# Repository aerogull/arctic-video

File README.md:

# Arctic-Video
#### An FPGA card designed around video, audio, and PCIe.
Built on a Xilinx Artix-7 75T FPGA chip, with jtag programming, video and audio ports on the card, and DDR3L RAM.

- XC7A75T-2FGG676C
- 256Mb spi flash
- 1GB DDR3L RAM
- 2 6G-SDI ports
- 1 2-lane DisplayPort
- PCIe gen 2 x4 interface
- JTAG programming
- 6 status LEDs

This hardware is untested, use the designs at your own risk!

An interactive bom, which includes jlc estimated prices, can be found in the ibom.html file in root. There is a full blend file and a file for the pcb bracket in the cad folder.

JLCPCB estimates:

PCB production costs $165.41

PCBA costs $392.47

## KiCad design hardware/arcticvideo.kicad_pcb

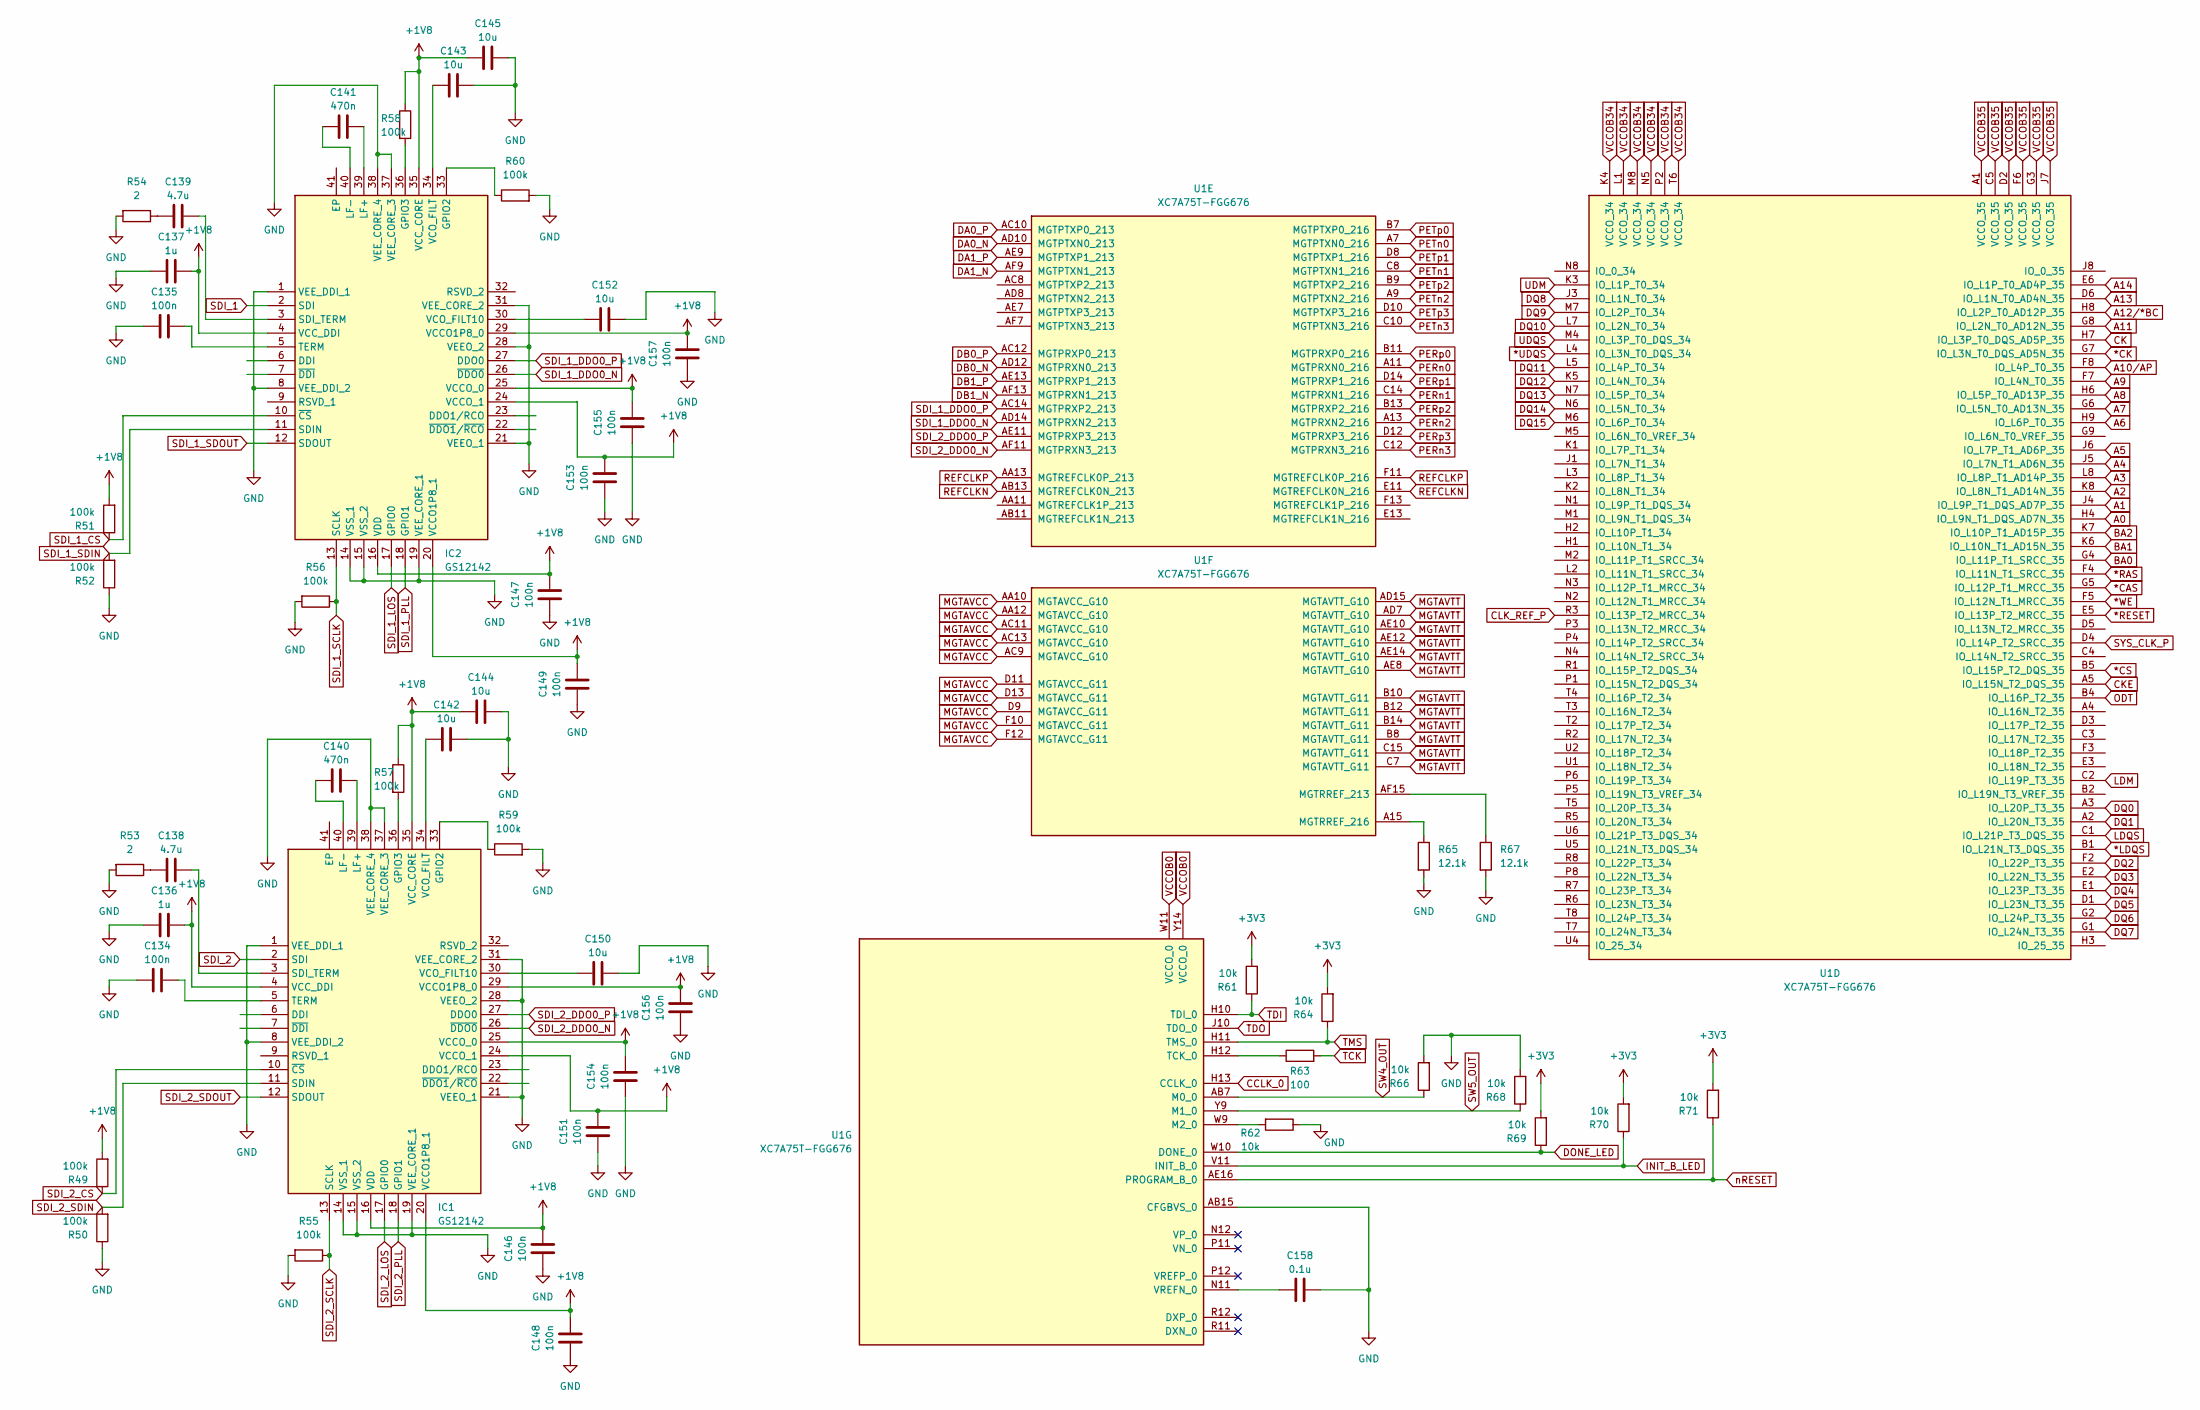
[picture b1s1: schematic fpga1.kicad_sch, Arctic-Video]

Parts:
C134, C135, C146, C147, C148, C149, C151, C153, C154, C155, C156, C157: 100n; C_0402_1005Metric
C136, C137: 1u; C_0402_1005Metric
C138, C139: 4.7u; C_0402_1005Metric
C140, C141: 470n; C_0402_1005Metric
C142, C143, C144, C145, C150, C152: 10u; C_0402_1005Metric
C158: 0.1u; C_0402_1005Metric
IC1, IC2: GS12142; QFN40P400X600X100-41N-D; Manufacturer_Part_Number GS12142
R49, R50, R51, R52, R55, R56, R57, R58, R59, R60: 100k; R_0402_1005Metric
R53, R54: 2; R_0402_1005Metric
R61, R62, R64, R66, R68, R69, R70, R71: 10k; R_0402_1005Metric
R63: 100; R_0402_1005Metric
R65, R67: 12.1k; R_0402_1005Metric
U1: XC7A75T-FGG676; Xilinx_FGG676

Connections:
*CAS: U1.G5 (IO_L12P_T1_MRCC_35); also elsewhere on the board
*CK: U1.G7 (IO_L3N_T0_DQS_AD5N_35); also elsewhere on the board
*CS: U1.B5 (IO_L15P_T2_DQS_35); also elsewhere on the board
*LDQS: U1.B1 (IO_L21N_T3_DQS_35); also elsewhere on the board
*RAS: U1.F4 (IO_L11N_T1_SRCC_35); also elsewhere on the board
*RESET: U1.E5 (IO_L13P_T2_MRCC_35); also elsewhere on the board
*UDQS: U1.L4 (IO_L3N_T0_DQS_34); also elsewhere on the board
*WE: U1.F5 (IO_L12N_T1_MRCC_35); also elsewhere on the board
A0: U1.H4 (IO_L9N_T1_DQS_AD7N_35); also elsewhere on the board
A1: U1.J4 (IO_L9P_T1_DQS_AD7P_35); also elsewhere on the board
A2: U1.K8 (IO_L8N_T1_AD14N_35); also elsewhere on the board
A3: U1.L8 (IO_L8P_T1_AD14P_35); also elsewhere on the board
A4: U1.J5 (IO_L7N_T1_AD6N_35); also elsewhere on the board
A5: U1.J6 (IO_L7P_T1_AD6P_35); also elsewhere on the board
A6: U1.H9 (IO_L6P_T0_35); also elsewhere on the board
A7: U1.G6 (IO_L5N_T0_AD13N_35); also elsewhere on the board
A8: U1.H6 (IO_L5P_T0_AD13P_35); also elsewhere on the board
A9: U1.F7 (IO_L4N_T0_35); also elsewhere on the board
A10/AP: U1.F8 (IO_L4P_T0_35); also elsewhere on the board
A11: U1.G8 (IO_L2N_T0_AD12N_35); also elsewhere on the board
A12/*BC: U1.H8 (IO_L2P_T0_AD12P_35); also elsewhere on the board
A13: U1.D6 (IO_L1N_T0_AD4N_35); also elsewhere on the board
A14: U1.E6 (IO_L1P_T0_AD4P_35); also elsewhere on the board
BA0: U1.G4 (IO_L11P_T1_SRCC_35); also elsewhere on the board
BA1: U1.K6 (IO_L10N_T1_AD15N_35); also elsewhere on the board
BA2: U1.K7 (IO_L10P_T1_AD15P_35); also elsewhere on the board
CCLK_0: U1.H13 (CCLK_0); also elsewhere on the board
CK: U1.H7 (IO_L3P_T0_DQS_AD5P_35); also elsewhere on the board
CKE: U1.A5 (IO_L15N_T2_DQS_35); also elsewhere on the board
CLK_REF_P: U1.D4 (IO_L14P_T2_SRCC_35), U1.R3 (IO_L13P_T2_MRCC_34); also elsewhere on the board
DA0_N: U1.AD10 (MGTPTXN0_213); also elsewhere on the board
DA0_P: U1.AC10 (MGTPTXP0_213); also elsewhere on the board
DA1_N: U1.AF9 (MGTPTXN1_213); also elsewhere on the board
DA1_P: U1.AE9 (MGTPTXP1_213); also elsewhere on the board
DB0_N: U1.AD12 (MGTPRXN0_213); also elsewhere on the board
DB0_P: U1.AC12 (MGTPRXP0_213); also elsewhere on the board
DB1_N: U1.AF13 (MGTPRXN1_213); also elsewhere on the board
DB1_P: U1.AE13 (MGTPRXP1_213); also elsewhere on the board
DONE_LED: R69.1, U1.W10 (DONE_0); also elsewhere on the board
DQ0: U1.A3 (IO_L20P_T3_35); also elsewhere on the board
DQ1: U1.A2 (IO_L20N_T3_35); also elsewhere on the board
DQ2: U1.F2 (IO_L22P_T3_35); also elsewhere on the board
DQ3: U1.E2 (IO_L22N_T3_35); also elsewhere on the board
DQ4: U1.E1 (IO_L23P_T3_35); also elsewhere on the board
DQ5: U1.D1 (IO_L23N_T3_35); also elsewhere on the board
DQ6: U1.G2 (IO_L24P_T3_35); also elsewhere on the board
DQ7: U1.G1 (IO_L24N_T3_35); also elsewhere on the board
DQ8: U1.J3 (IO_L1N_T0_34); also elsewhere on the board
DQ9: U1.M7 (IO_L2P_T0_34); also elsewhere on the board
DQ10: U1.L7 (IO_L2N_T0_34); also elsewhere on the board
DQ11: U1.L5 (IO_L4P_T0_34); also elsewhere on the board
DQ12: U1.K5 (IO_L4N_T0_34); also elsewhere on the board
DQ13: U1.N7 (IO_L5P_T0_34); also elsewhere on the board
DQ14: U1.N6 (IO_L5N_T0_34); also elsewhere on the board
DQ15: U1.M6 (IO_L6P_T0_34); also elsewhere on the board
GND: C134.1, C135.1, C136.1, C137.1, C142.2, C143.2, C144.2, C145.2, C146.1, C147.1, C148.1, C149.1, C150.2, C151.1, C152.2, C153.1, C154.1, C155.1, C156.1, C157.1, C158.2, IC1.1 (VEE_DDI_1), IC1.8 (VEE_DDI_2), IC1.14 (VSS_1), IC1.15 (VSS_2), IC1.19 (VEE_CORE_1), IC1.21 (VEEO_1), IC1.28 (VEEO_2), IC1.31 (VEE_CORE_2), IC1.37 (VEE_CORE_3), IC1.38 (VEE_CORE_4), IC2.1 (VEE_DDI_1), IC2.8 (VEE_DDI_2), IC2.14 (VSS_1), IC2.15 (VSS_2), IC2.19 (VEE_CORE_1), IC2.21 (VEEO_1), IC2.28 (VEEO_2), IC2.31 (VEE_CORE_2), IC2.37 (VEE_CORE_3), IC2.38 (VEE_CORE_4), R50.1, R52.1, R53.2, R54.2, R55.2, R56.2, R59.2, R60.2, R62.1, R65.2, R66.2, R67.2, R68.2, U1.AB15 (CFGBVS_0); also elsewhere on the board
INIT_B_LED: R70.1, U1.V11 (INIT_B_0); also elsewhere on the board
LDM: U1.C2 (IO_L19P_T3_35); also elsewhere on the board
LDQS: U1.C1 (IO_L21P_T3_DQS_35); also elsewhere on the board
MGTAVCC: U1.AA10 (MGTAVCC_G10), U1.AA12 (MGTAVCC_G10), U1.AC9 (MGTAVCC_G10), U1.AC11 (MGTAVCC_G10), U1.AC13 (MGTAVCC_G10), U1.D9 (MGTAVCC_G11), U1.D11 (MGTAVCC_G11), U1.D13 (MGTAVCC_G11), U1.F10 (MGTAVCC_G11), U1.F12 (MGTAVCC_G11); also elsewhere on the board
MGTAVTT: U1.AD7 (MGTAVTT_G10), U1.AD15 (MGTAVTT_G10), U1.AE8 (MGTAVTT_G10), U1.AE10 (MGTAVTT_G10), U1.AE12 (MGTAVTT_G10), U1.AE14 (MGTAVTT_G10), U1.B8 (MGTAVTT_G11), U1.B10 (MGTAVTT_G11), U1.B12 (MGTAVTT_G11), U1.B14 (MGTAVTT_G11), U1.C7 (MGTAVTT_G11), U1.C15 (MGTAVTT_G11); also elsewhere on the board
unnamed: C138.1, R53.1
unnamed: C139.1, R54.1
unnamed: IC1.33 (GPIO2), R59.1
unnamed: IC1.36 (GPIO3), R57.2
unnamed: C140.2, IC1.39 (LF+)
unnamed: C140.1, IC1.40 (LF-)
unnamed: C138.2, IC1.3 (SDI_TERM)
unnamed: C134.2, IC1.5 (TERM)
unnamed: C150.1, IC1.30 (VCO_FILT10)
unnamed: C142.1, IC1.34 (VCO_FILT)
unnamed: IC2.33 (GPIO2), R60.1
unnamed: IC2.36 (GPIO3), R58.2
unnamed: C141.2, IC2.39 (LF+)
unnamed: C141.1, IC2.40 (LF-)
unnamed: C139.2, IC2.3 (SDI_TERM)
unnamed: C135.2, IC2.5 (TERM)
unnamed: C152.1, IC2.30 (VCO_FILT10)
unnamed: C143.1, IC2.34 (VCO_FILT)
unnamed: R67.1, U1.AF15 (MGTRREF_213)
unnamed: R65.1, U1.A15 (MGTRREF_216)
unnamed: R62.2, U1.W9 (M2_0)
unnamed: R63.1, U1.H12 (TCK_0)
unnamed: C158.1, U1.N11 (VREFN_0)
ODT: U1.B4 (IO_L16P_T2_35); also elsewhere on the board
PERn0: U1.A11 (MGTPRXN0_216); also elsewhere on the board
PERn1: U1.C14 (MGTPRXN1_216); also elsewhere on the board
PERn2: U1.A13 (MGTPRXN2_216); also elsewhere on the board
PERn3: U1.C12 (MGTPRXN3_216); also elsewhere on the board
PERp0: U1.B11 (MGTPRXP0_216); also elsewhere on the board
PERp1: U1.D14 (MGTPRXP1_216); also elsewhere on the board
PERp2: U1.B13 (MGTPRXP2_216); also elsewhere on the board
PERp3: U1.D12 (MGTPRXP3_216); also elsewhere on the board
PETn0: U1.A7 (MGTPTXN0_216); also elsewhere on the board
PETn1: U1.C8 (MGTPTXN1_216); also elsewhere on the board
PETn2: U1.A9 (MGTPTXN2_216); also elsewhere on the board
PETn3: U1.C10 (MGTPTXN3_216); also elsewhere on the board
PETp0: U1.B7 (MGTPTXP0_216); also elsewhere on the board
PETp1: U1.D8 (MGTPTXP1_216); also elsewhere on the board
PETp2: U1.B9 (MGTPTXP2_216); also elsewhere on the board
PETp3: U1.D10 (MGTPTXP3_216); also elsewhere on the board
REFCLKN: U1.AB13 (MGTREFCLK0N_213), U1.E11 (MGTREFCLK0N_216); also elsewhere on the board
REFCLKP: U1.AA13 (MGTREFCLK0P_213), U1.F11 (MGTREFCLK0P_216); also elsewhere on the board
SDI_1: IC2.2 (SDI); also elsewhere on the board
SDI_1_CS: IC2.10 (~CS), R51.1; also elsewhere on the board
SDI_1_DDO0_N: IC2.26 (~DDO0), U1.AD14 (MGTPRXN2_213)
SDI_1_DDO0_P: IC2.27 (DDO0), U1.AC14 (MGTPRXP2_213)
SDI_1_LOS: IC2.17 (GPIO0); also elsewhere on the board
SDI_1_PLL: IC2.18 (GPIO1); also elsewhere on the board
SDI_1_SCLK: IC2.13 (SCLK), R56.1; also elsewhere on the board
SDI_1_SDIN: IC2.11 (SDIN), R52.2; also elsewhere on the board
SDI_1_SDOUT: IC2.12 (SDOUT); also elsewhere on the board
SDI_2: IC1.2 (SDI); also elsewhere on the board
SDI_2_CS: IC1.10 (~CS), R49.1; also elsewhere on the board
SDI_2_DDO0_N: IC1.26 (~DDO0), U1.AF11 (MGTPRXN3_213)
SDI_2_DDO0_P: IC1.27 (DDO0), U1.AE11 (MGTPRXP3_213)
SDI_2_LOS: IC1.17 (GPIO0); also elsewhere on the board
SDI_2_PLL: IC1.18 (GPIO1); also elsewhere on the board
SDI_2_SCLK: IC1.13 (SCLK), R55.1; also elsewhere on the board
SDI_2_SDIN: IC1.11 (SDIN), R50.2; also elsewhere on the board
SDI_2_SDOUT: IC1.12 (SDOUT); also elsewhere on the board
SW4_OUT: R66.1, U1.AB7 (M0_0); also elsewhere on the board
SW5_OUT: R68.1, U1.Y9 (M1_0); also elsewhere on the board
TCK: R63.2; also elsewhere on the board
TDI: R61.1, U1.H10 (TDI_0); also elsewhere on the board
TDO: U1.J10 (TDO_0); also elsewhere on the board
TMS: R64.1, U1.H11 (TMS_0); also elsewhere on the board
UDM: U1.K3 (IO_L1P_T0_34); also elsewhere on the board
UDQS: U1.M4 (IO_L3P_T0_DQS_34); also elsewhere on the board
VCCAUX: C136.2, C137.2, C144.1, C145.1, C146.2, C147.2, C148.2, C149.2, C151.2, C153.2, C154.2, C155.2, C156.2, C157.2, IC1.4 (VCC_DDI), IC1.16 (VDD), IC1.20 (VCCO1P8_1), IC1.24 (VCCO_1), IC1.25 (VCCO_0), IC1.29 (VCCO1P8_0), IC1.35 (VCC_CORE), IC2.4 (VCC_DDI), IC2.16 (VDD), IC2.20 (VCCO1P8_1), IC2.24 (VCCO_1), IC2.25 (VCCO_0), IC2.29 (VCCO1P8_0), IC2.35 (VCC_CORE), R49.2, R51.2, R57.1, R58.1; also elsewhere on the board
VCCOB0: R61.2, R64.2, R69.2, R70.2, R71.2, U1.W11 (VCCO_0), U1.Y14 (VCCO_0); also elsewhere on the board
VCCOB33: U1.A1 (VCCO_35), U1.C5 (VCCO_35), U1.D2 (VCCO_35), U1.F6 (VCCO_35), U1.G3 (VCCO_35), U1.J7 (VCCO_35), U1.K4 (VCCO_34), U1.L1 (VCCO_34), U1.M8 (VCCO_34), U1.N5 (VCCO_34), U1.P2 (VCCO_34), U1.T6 (VCCO_34); also elsewhere on the board
nRESET: R71.1, U1.AE16 (PROGRAM_B_0); also elsewhere on the board

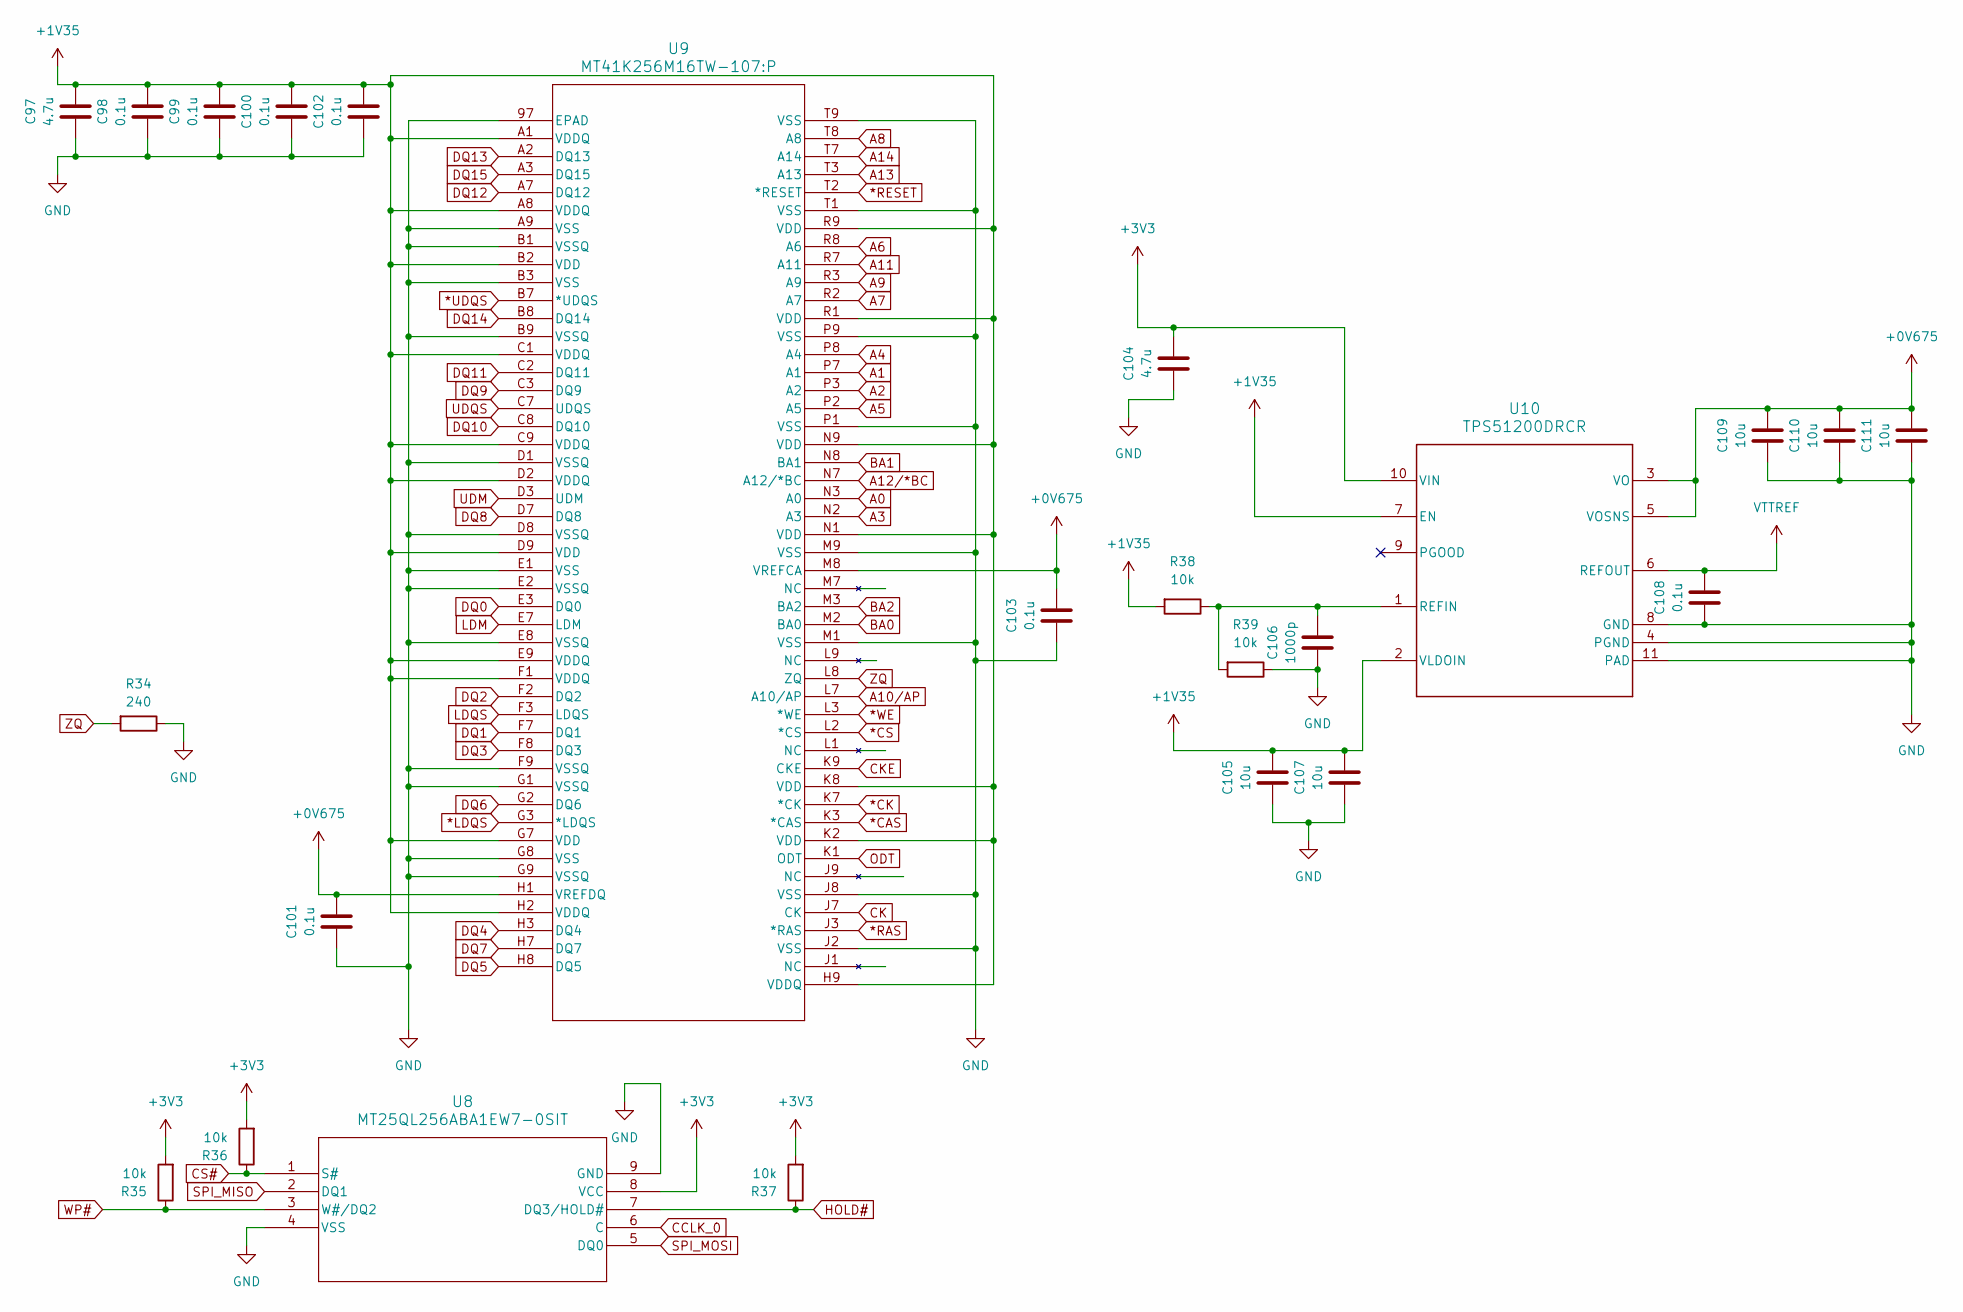
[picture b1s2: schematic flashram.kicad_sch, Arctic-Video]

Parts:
C97, C104: 4.7u; C_0402_1005Metric
C98, C99, C100, C101, C102, C103, C108: 0.1u; C_0402_1005Metric
C105, C107, C109, C110, C111: 10u; C_0402_1005Metric
C106: 1000p; C_0402_1005Metric
R34: 240; R_0402_1005Metric
R35, R36, R37, R38, R39: 10k; R_0402_1005Metric
U8: MT25QL256ABA1EW7-0SIT; SON_EW7-0SIT_MRN
U9: MT41K256M16TW-107:P; FBGA96_8X14_MRN
U10: TPS51200DRCR; DRC0010J

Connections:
*CAS: U9.K3 (*CAS); also elsewhere on the board
*CK: U9.K7 (*CK); also elsewhere on the board
*CS: U9.L2 (*CS); also elsewhere on the board
*LDQS: U9.G3 (*LDQS); also elsewhere on the board
*RAS: U9.J3 (*RAS); also elsewhere on the board
*RESET: U9.T2 (*RESET); also elsewhere on the board
*UDQS: U9.B7 (*UDQS); also elsewhere on the board
*WE: U9.L3 (*WE); also elsewhere on the board
+0V675: C101.2, C103.2, C109.2, C110.2, C111.2, U9.H1 (VREFDQ), U9.M8 (VREFCA), U10.3 (VO), U10.5 (VOSNS)
A0: U9.N3 (A0); also elsewhere on the board
A1: U9.P7 (A1); also elsewhere on the board
A2: U9.P3 (A2); also elsewhere on the board
A3: U9.N2 (A3); also elsewhere on the board
A4: U9.P8 (A4); also elsewhere on the board
A5: U9.P2 (A5); also elsewhere on the board
A6: U9.R8 (A6); also elsewhere on the board
A7: U9.R2 (A7); also elsewhere on the board
A8: U9.T8 (A8); also elsewhere on the board
A9: U9.R3 (A9); also elsewhere on the board
A10/AP: U9.L7 (A10/AP); also elsewhere on the board
A11: U9.R7 (A11); also elsewhere on the board
A12/*BC: U9.N7 (A12/*BC); also elsewhere on the board
A13: U9.T3 (A13); also elsewhere on the board
A14: U9.T7 (A14); also elsewhere on the board
BA0: U9.M2 (BA0); also elsewhere on the board
BA1: U9.N8 (BA1); also elsewhere on the board
BA2: U9.M3 (BA2); also elsewhere on the board
CCLK_0: U8.6 (C); also elsewhere on the board
CK: U9.J7 (CK); also elsewhere on the board
CKE: U9.K9 (CKE); also elsewhere on the board
CS#: R36.1, U8.1 (S#); also elsewhere on the board
DQ0: U9.E3 (DQ0); also elsewhere on the board
DQ1: U9.F7 (DQ1); also elsewhere on the board
DQ2: U9.F2 (DQ2); also elsewhere on the board
DQ3: U9.F8 (DQ3); also elsewhere on the board
DQ4: U9.H3 (DQ4); also elsewhere on the board
DQ5: U9.H8 (DQ5); also elsewhere on the board
DQ6: U9.G2 (DQ6); also elsewhere on the board
DQ7: U9.H7 (DQ7); also elsewhere on the board
DQ8: U9.D7 (DQ8); also elsewhere on the board
DQ9: U9.C3 (DQ9); also elsewhere on the board
DQ10: U9.C8 (DQ10); also elsewhere on the board
DQ11: U9.C2 (DQ11); also elsewhere on the board
DQ12: U9.A7 (DQ12); also elsewhere on the board
DQ13: U9.A2 (DQ13); also elsewhere on the board
DQ14: U9.B8 (DQ14); also elsewhere on the board
DQ15: U9.A3 (DQ15); also elsewhere on the board
GND: C97.1, C98.1, C99.1, C100.1, C101.1, C102.1, C103.1, C104.1, C105.1, C106.1, C107.1, C108.1, C109.1, C110.1, C111.1, R34.1, R39.1, U8.4 (VSS), U8.9 (GND), U9.97 (EPAD), U9.A9 (VSS), U9.B1 (VSSQ), U9.B3 (VSS), U9.B9 (VSSQ), U9.D1 (VSSQ), U9.D8 (VSSQ), U9.E1 (VSS), U9.E2 (VSSQ), U9.E8 (VSSQ), U9.F9 (VSSQ), U9.G1 (VSSQ), U9.G8 (VSS), U9.G9 (VSSQ), U9.J2 (VSS), U9.J8 (VSS), U9.M1 (VSS), U9.M9 (VSS), U9.P1 (VSS), U9.P9 (VSS), U9.T1 (VSS), U9.T9 (VSS), U10.4 (PGND), U10.8 (GND), U10.11 (PAD); also elsewhere on the board
HOLD#: R37.1, U8.7 (DQ3/HOLD#); also elsewhere on the board
LDM: U9.E7 (LDM); also elsewhere on the board
LDQS: U9.F3 (LDQS); also elsewhere on the board
unnamed: C106.2, R38.1, R39.2, U10.1 (REFIN)
ODT: U9.K1 (ODT); also elsewhere on the board
SPI_MISO: U8.2 (DQ1); also elsewhere on the board
SPI_MOSI: U8.5 (DQ0); also elsewhere on the board
UDM: U9.D3 (UDM); also elsewhere on the board
UDQS: U9.C7 (UDQS); also elsewhere on the board
VCCOB0: C104.2, R35.2, R36.2, R37.2, U8.8 (VCC), U10.10 (VIN); also elsewhere on the board
VCCOB33: C97.2, C98.2, C99.2, C100.2, C102.2, C105.2, C107.2, R38.2, U9.A1 (VDDQ), U9.A8 (VDDQ), U9.B2 (VDD), U9.C1 (VDDQ), U9.C9 (VDDQ), U9.D2 (VDDQ), U9.D9 (VDD), U9.E9 (VDDQ), U9.F1 (VDDQ), U9.G7 (VDD), U9.H2 (VDDQ), U9.H9 (VDDQ), U9.K2 (VDD), U9.K8 (VDD), U9.N1 (VDD), U9.N9 (VDD), U9.R1 (VDD), U9.R9 (VDD), U10.2 (VLDOIN), U10.7 (EN); also elsewhere on the board
VTTREF: C108.2, U10.6 (REFOUT)
WP#: R35.1, U8.3 (W#/DQ2); also elsewhere on the board
ZQ: R34.2, U9.L8 (ZQ)

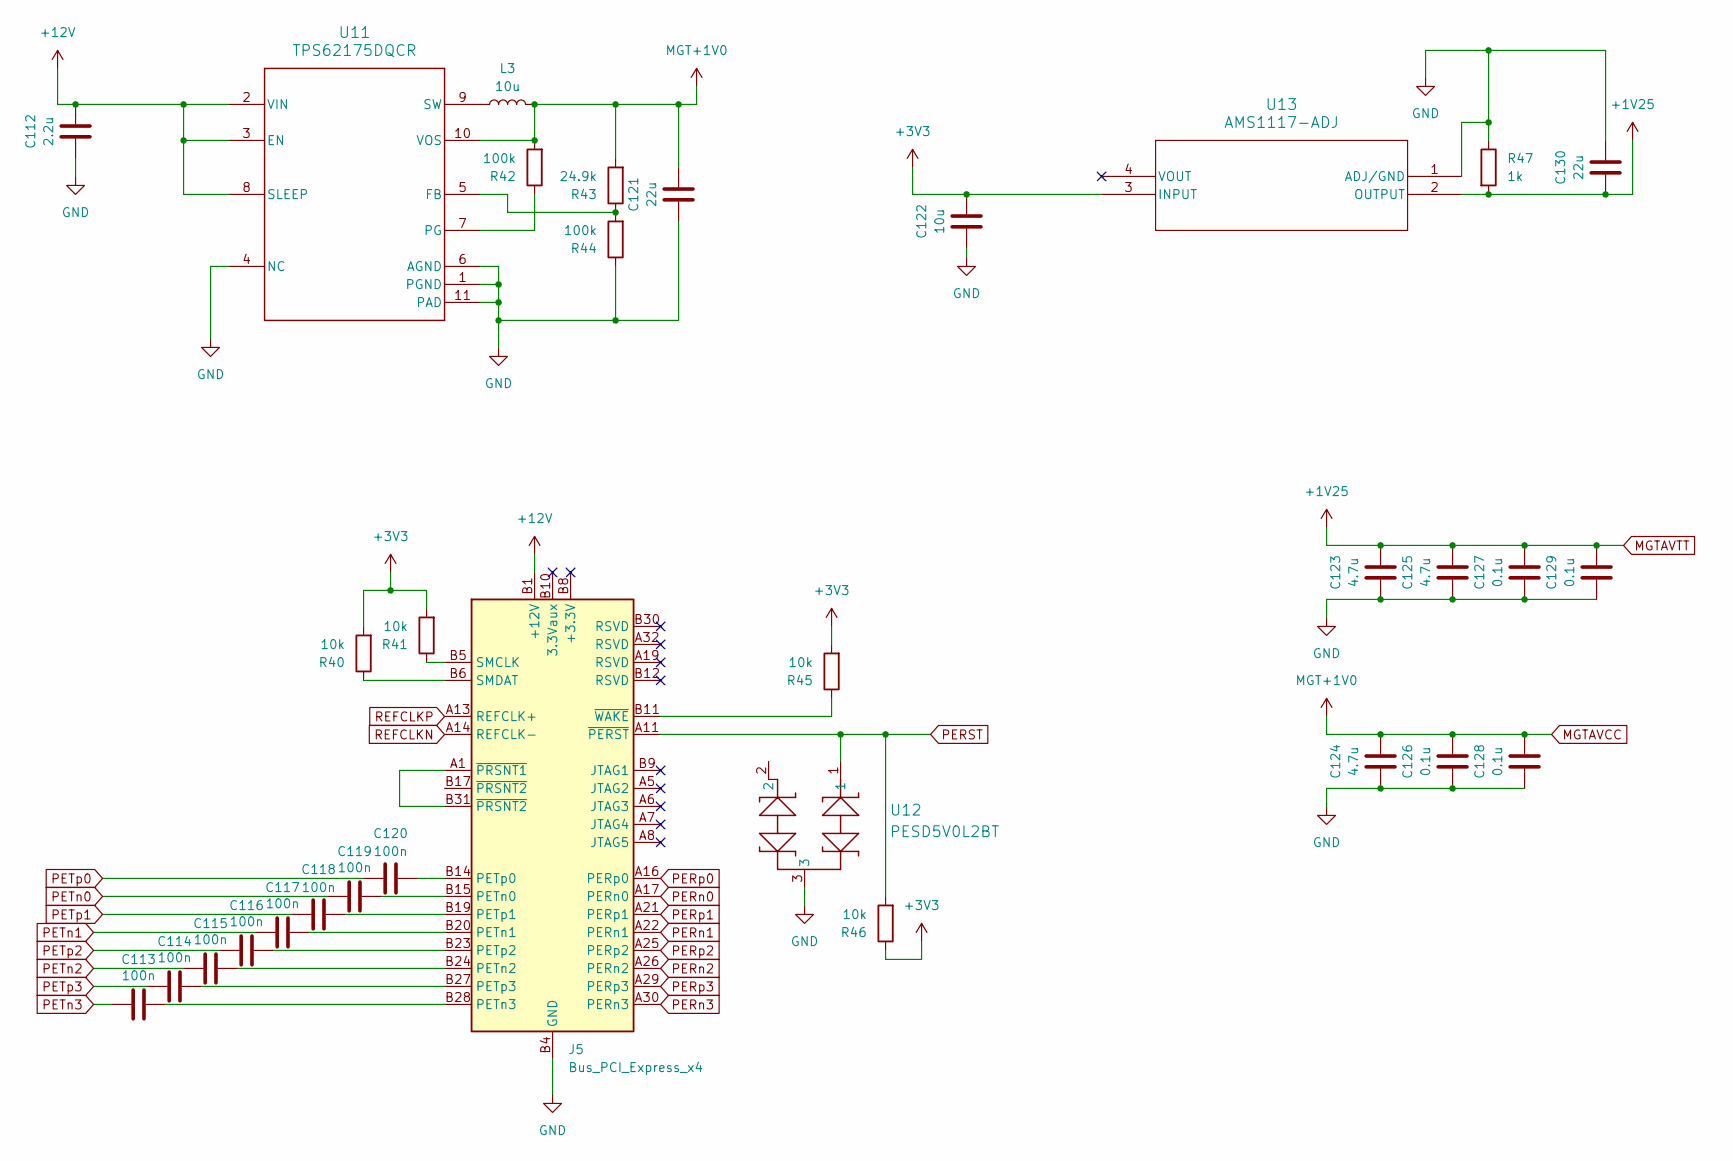
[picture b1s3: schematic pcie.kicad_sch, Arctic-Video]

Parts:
C112: 2.2u; C_0402_1005Metric
C113, C114, C115, C116, C117, C118, C119, C120: 100n; C_0402_1005Metric
C121, C130: 22u; C_0402_1005Metric
C122: 10u; C_0402_1005Metric
C123, C124, C125: 4.7u; C_0402_1005Metric
C126, C127, C128, C129: 0.1u; C_0402_1005Metric
J5: Bus_PCI_Express_x4; BUS_PCIexpress_x4
L3: 10u; L_0402_1005Metric
R40, R41, R45, R46: 10k; R_0402_1005Metric
R42, R44: 100k; R_0402_1005Metric
R43: 24.9k; R_0402_1005Metric
R47: 1k; R_0402_1005Metric
U11: TPS62175DQCR; DQC0010A
U12: PESD5V0L2BT; SOT23_NEX
U13: AMS1117-ADJ; SOT_AMS1117-2.5_AMS

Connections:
+12V: C112.2, J5.A2 (+12V), J5.A3 (+12V), J5.B1 (+12V), J5.B2 (+12V), J5.B3 (+12V), U11.2 (VIN), U11.3 (EN), U11.8 (SLEEP); also elsewhere on the board
GND: C112.1, C121.1, C122.1, C123.1, C124.1, C125.1, C126.1, C127.1, C128.1, C129.1, C130.2, J5.A4 (GND), J5.A12 (GND), J5.A15 (GND), J5.A18 (GND), J5.A20 (GND), J5.A23 (GND), J5.A24 (GND), J5.A27 (GND), J5.A28 (GND), J5.A31 (GND), J5.B4 (GND), J5.B7 (GND), J5.B13 (GND), J5.B16 (GND), J5.B18 (GND), J5.B21 (GND), J5.B22 (GND), J5.B25 (GND), J5.B26 (GND), J5.B29 (GND), J5.B32 (GND), R44.1, R47.1, U11.1 (PGND), U11.4 (NC), U11.6 (AGND), U11.11 (PAD), U12.3, U13.1 (ADJ/GND); also elsewhere on the board
MGTAVCC: C121.2, C124.2, C126.2, C128.2, L3.2, R42.2, R43.2, U11.10 (VOS); also elsewhere on the board
MGTAVTT: C123.2, C125.2, C127.2, C129.2, C130.1, R47.2, U13.2 (OUTPUT); also elsewhere on the board
unnamed: C119.2, J5.B15 (PETn0)
unnamed: C117.2, J5.B20 (PETn1)
unnamed: C115.2, J5.B24 (PETn2)
unnamed: C113.2, J5.B28 (PETn3)
unnamed: C120.2, J5.B14 (PETp0)
unnamed: C118.2, J5.B19 (PETp1)
unnamed: C116.2, J5.B23 (PETp2)
unnamed: C114.2, J5.B27 (PETp3)
unnamed: J5.B5 (SMCLK), R41.1
unnamed: J5.B6 (SMDAT), R40.1
unnamed: J5.A1 (~PRSNT1), J5.B31 (~PRSNT2)
unnamed: J5.B11 (~WAKE), R45.1
unnamed: R43.1, R44.2, U11.5 (FB)
unnamed: R42.1, U11.7 (PG)
unnamed: L3.1, U11.9 (SW)
PERST: J5.A11 (~PERST), R46.2, U12.1; also elsewhere on the board
PERn0: J5.A17 (PERn0); also elsewhere on the board
PERn1: J5.A22 (PERn1); also elsewhere on the board
PERn2: J5.A26 (PERn2); also elsewhere on the board
PERn3: J5.A30 (PERn3); also elsewhere on the board
PERp0: J5.A16 (PERp0); also elsewhere on the board
PERp1: J5.A21 (PERp1); also elsewhere on the board
PERp2: J5.A25 (PERp2); also elsewhere on the board
PERp3: J5.A29 (PERp3); also elsewhere on the board
PETn0: C119.1; also elsewhere on the board
PETn1: C117.1; also elsewhere on the board
PETn2: C115.1; also elsewhere on the board
PETn3: C113.1; also elsewhere on the board
PETp0: C120.1; also elsewhere on the board
PETp1: C118.1; also elsewhere on the board
PETp2: C116.1; also elsewhere on the board
PETp3: C114.1; also elsewhere on the board
REFCLKN: J5.A14 (REFCLK-); also elsewhere on the board
REFCLKP: J5.A13 (REFCLK+); also elsewhere on the board
VCCOB0: C122.2, R40.2, R41.2, R45.2, R46.1, U13.3 (INPUT); also elsewhere on the board
